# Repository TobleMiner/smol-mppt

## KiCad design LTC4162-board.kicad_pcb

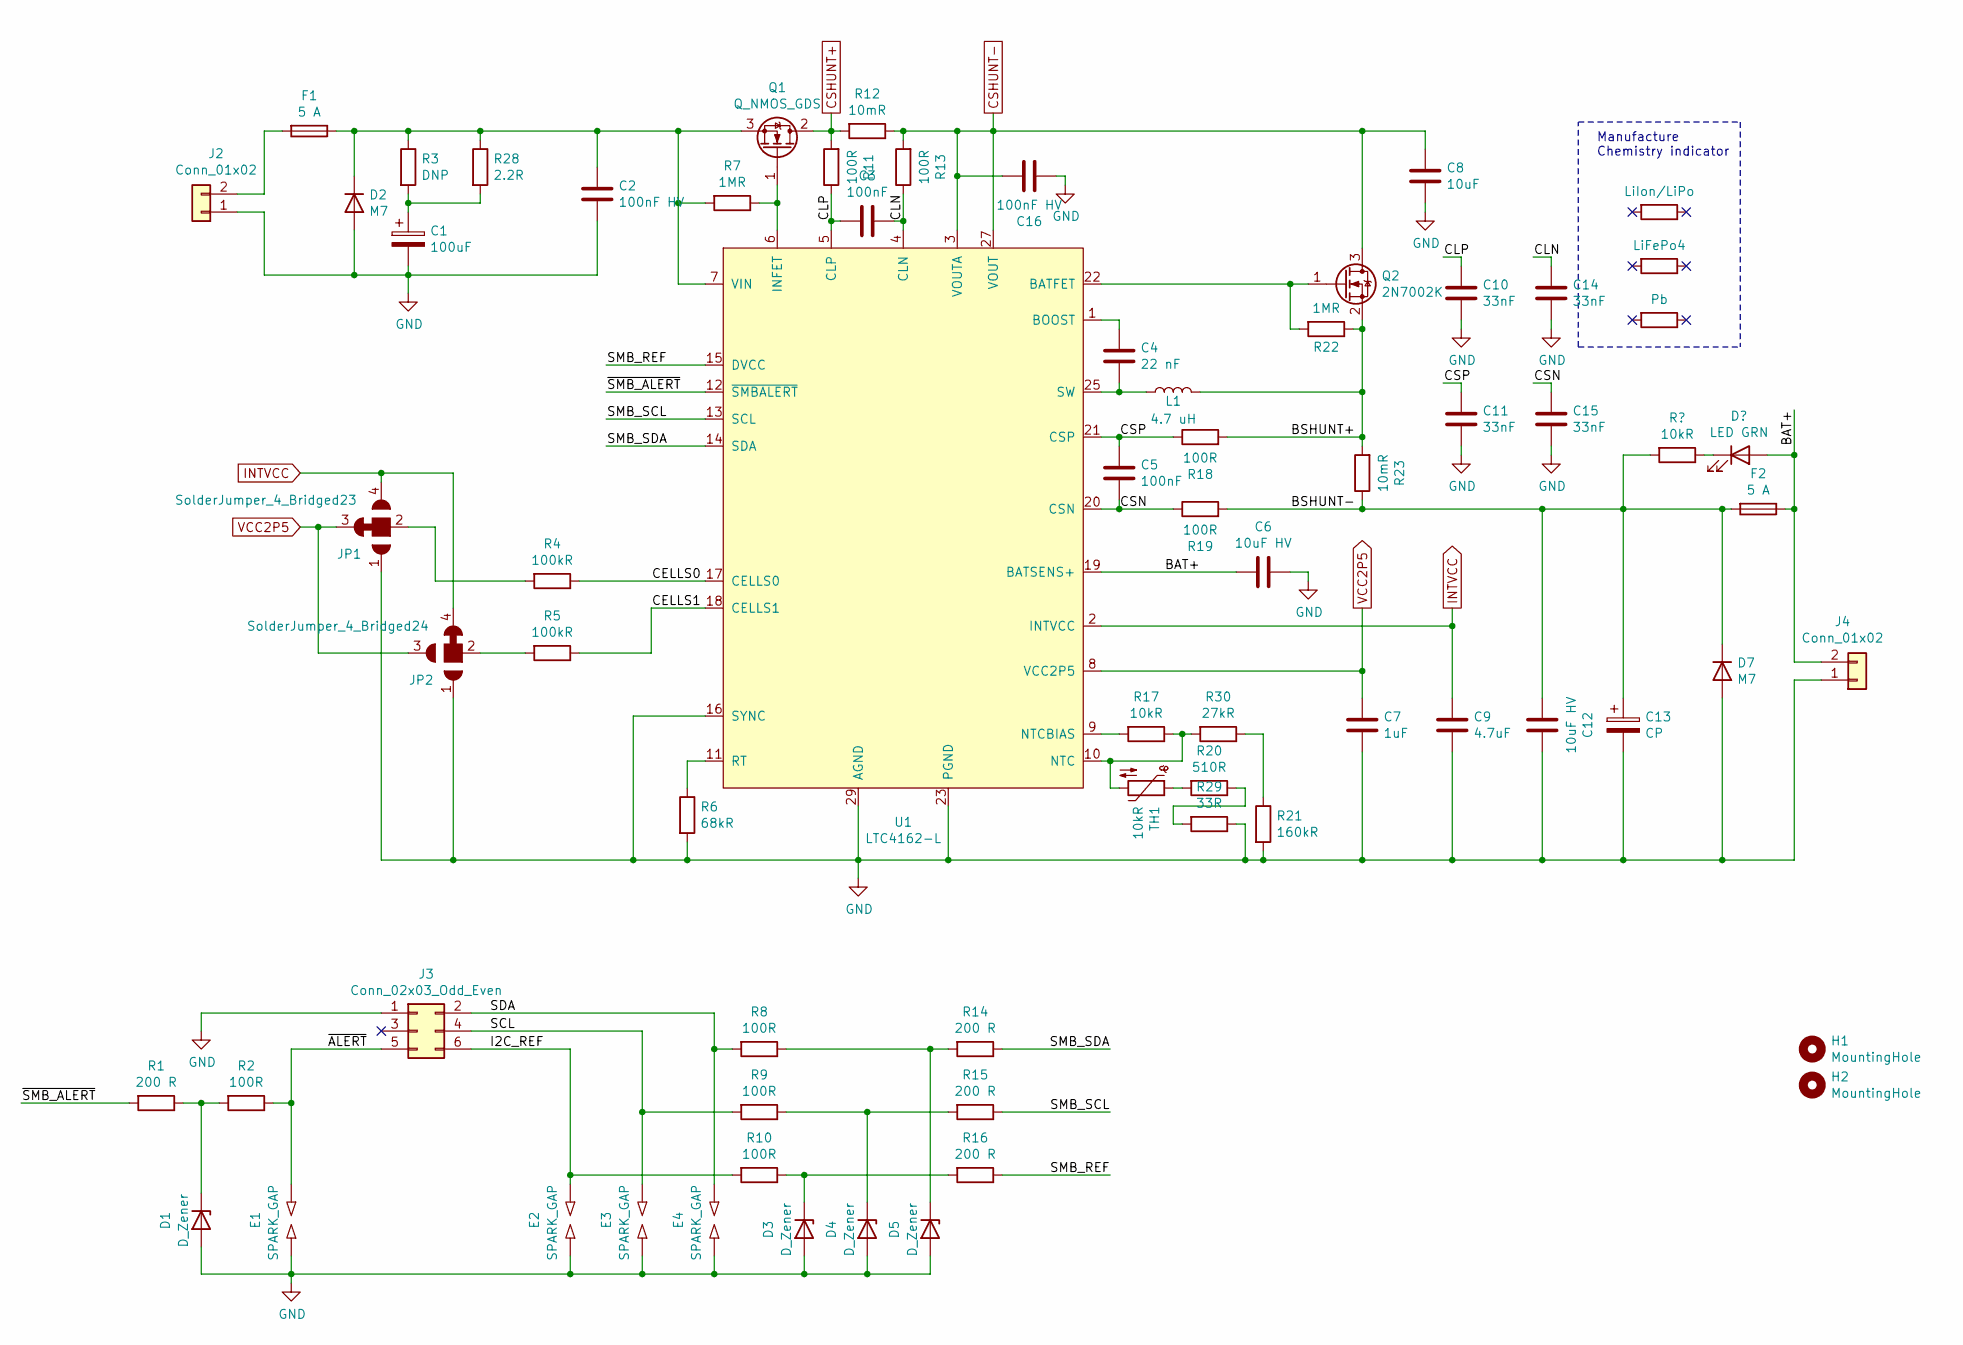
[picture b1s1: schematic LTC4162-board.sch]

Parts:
C1: 100uF; CP_Elec_10x10; LCSC C249996
C2, C16: 100nF HV; C_0603_1608Metric; LCSC C14663
C3, C5: 100nF; C_0402_1005Metric; LCSC C1525
C4: 22 nF; C_0402_1005Metric; LCSC C1532
C6, C12: 10uF HV; C_1206_3216Metric; LCSC C13585
C7: 1uF; C_0402_1005Metric; LCSC C52923
C8: 10uF; C_1206_3216Metric; LCSC C13585
C9: 4.7uF; C_0402_1005Metric; LCSC C23733
C10, C11, C14, C15: 33nF; C_0402_1005Metric; LCSC C1585
C13: CP; C_Elec_6.3x7.7; LCSC C249984
D1, D3, D4, D5: D_Zener; D_MiniMELF; LCSC C8062
D2, D7: M7; D_SMA; LCSC C95872
E1, E2, E3, E4: SPARK_GAP; spark-gap-0.2mm
F1, F2: 5 A; Fuse_1206_3216Metric; LCSC C182446
H1, H2: MountingHole; ToolingHole_JLCSMT
J2, J4: Conn_01x02; XT60
J3: Conn_02x03_Odd_Even; IDC-Header_2x03_P2.54mm_Vertical
JP1: SolderJumper_4_Bridged23; SolderJumper-4_P1.3mm_Bridged24_RoundedPad1.0x1.5mm
JP2: SolderJumper_4_Bridged24; SolderJumper-4_P1.3mm_Bridged23_RoundedPad1.0x1.5mm
L1: 4.7 uH; SLO0630H; LCSC C207840
Q1: Q_NMOS_GDS; TO-252-3_TabPin2; LCSC C194346
Q2: 2N7002K; SOT-23; LCSC C8545
R1, R14, R15, R16: 200 R; R_0402_1005Metric; LCSC C25087
R2, R8, R9, R10: 100R; R_0805_2012Metric; LCSC C17408
R3: DNP; R_1206_3216Metric
R4, R5: 100kR; R_0402_1005Metric; LCSC C25741
R6: 68kR; R_0402_1005Metric; LCSC C36871
R7, R22: 1MR; R_0402_1005Metric; LCSC C26083
R11, R13, R18, R19: 100R; R_0402_1005Metric; LCSC C25076
R12, R23: 10mR; R_1206_3216Metric; LCSC C26119
R17: 10kR; R_0402_1005Metric; LCSC C25744
R20: 510R; R_0402_1005Metric; LCSC C25123
R21: 160kR; R_0603_1608Metric; LCSC C22813
R24: LiIon/LiPo; R_0402_1005Metric
R25: LiFePo4; R_0402_1005Metric
R26: Pb; R_0402_1005Metric
R28: 2.2R; R_0805_2012Metric; LCSC C17521
R29: 33R; R_0402_1005Metric; LCSC C25105
R30: 27kR; R_0402_1005Metric; LCSC C25771
TH1: 10kR; R_0402_1005Metric; LCSC C92371
U1: LTC4162-L; QFN-28-1EP_4x5mm_P0.5mm_EP2.65x3.65mm_ThermalVias_backsolder

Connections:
/BAT+: C6.1, F2.1, J4.2, U1.19 (BATSENS+); also elsewhere on the board
/BSHUNT+: L1.2, Q2.2 (S), R18.2, R22.1, R23.2
/BSHUNT-: C12.1, C13.1, D7.1 (K), F2.2, R19.2, R23.1; also elsewhere on the board
/CELLS0: R4.1, U1.17 (CELLS0)
/CELLS1: R5.1, U1.18 (CELLS1)
/CLN: C3.2, C14.1, R13.1, U1.4 (CLN)
/CLP: C3.1, C10.1, R11.1, U1.5 (CLP)
/CSN: C5.2, C15.1, R19.1, U1.20 (CSN)
/CSP: C5.1, C11.1, R18.1, U1.21 (CSP)
/I2C_REF: E2.1, J3.6, R10.2
/SCL: E3.1, J3.4, R9.2
/SDA: E4.1, J3.2, R8.2
/SMB_REF: R16.1, U1.15 (DVCC)
/SMB_SCL: R15.1, U1.13 (SCL)
/SMB_SDA: R14.1, U1.14 (SDA)
/~ALERT: E1.1, J3.5, R2.1
/~SMB_ALERT: R1.2, U1.12 (~SMBALERT)
CSHUNT+: Q1.2 (D), R11.2, R12.2
CSHUNT-: C8.1, C16.2, Q2.3 (D), R12.1, R13.2, U1.3 (VOUTA), U1.27 (VOUT), U1.28 (VOUT)
GND: C1.2, C2.2, C6.2, C7.2, C8.2, C9.2, C10.2, C11.2, C12.2, C13.2, C14.2, C15.2, C16.1, D1.2 (A), D2.2 (A), D3.2 (A), D4.2 (A), D5.2 (A), D7.2 (A), E1.2, E2.2, E3.2, E4.2, J2.1, J3.1, J4.1, JP1.1, JP2.1, R6.2, R21.2, R29.1, U1.16 (SYNC), U1.23 (PGND), U1.24 (PGND), U1.29 (AGND)
INTVCC: C9.1, JP1.4, JP2.4, U1.2 (INTVCC)
unnamed: C1.1, R3.2, R28.2
unnamed: C2.1, D2.1 (K), F1.1, Q1.3 (S), R3.1, R7.2, R28.1, U1.7 (VIN)
unnamed: C4.1, U1.1 (BOOST)
unnamed: C4.2, L1.1, U1.25 (SW), U1.26 (SW)
unnamed: D1.1 (K), R1.1, R2.2
unnamed: D3.1 (K), R10.1, R16.2
unnamed: D4.1 (K), R9.1, R15.2
unnamed: D5.1 (K), R8.1, R14.2
unnamed: F1.2, J2.2
unnamed: JP1.2, R4.2
unnamed: JP2.2, R5.2
unnamed: Q1.1 (G), R7.1, U1.6 (INFET)
unnamed: Q2.1 (G), R22.2, U1.22 (BATFET)
unnamed: R6.1, U1.11 (RT)
unnamed: R17.1, R30.2, TH1.2, U1.10 (NTC)
unnamed: R17.2, U1.9 (NTCBIAS)
unnamed: R20.1, R29.2
unnamed: R20.2, TH1.1
unnamed: R21.1, R30.1
VCC2P5: C7.1, JP1.3, JP2.3, U1.8 (VCC2P5)

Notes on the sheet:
Manufacture Chemistry indicator

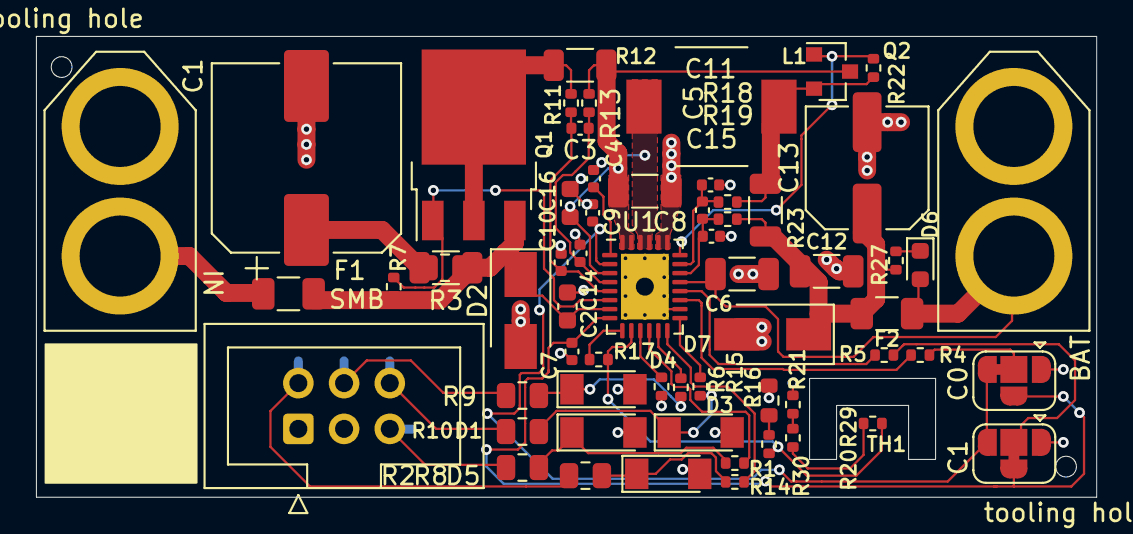
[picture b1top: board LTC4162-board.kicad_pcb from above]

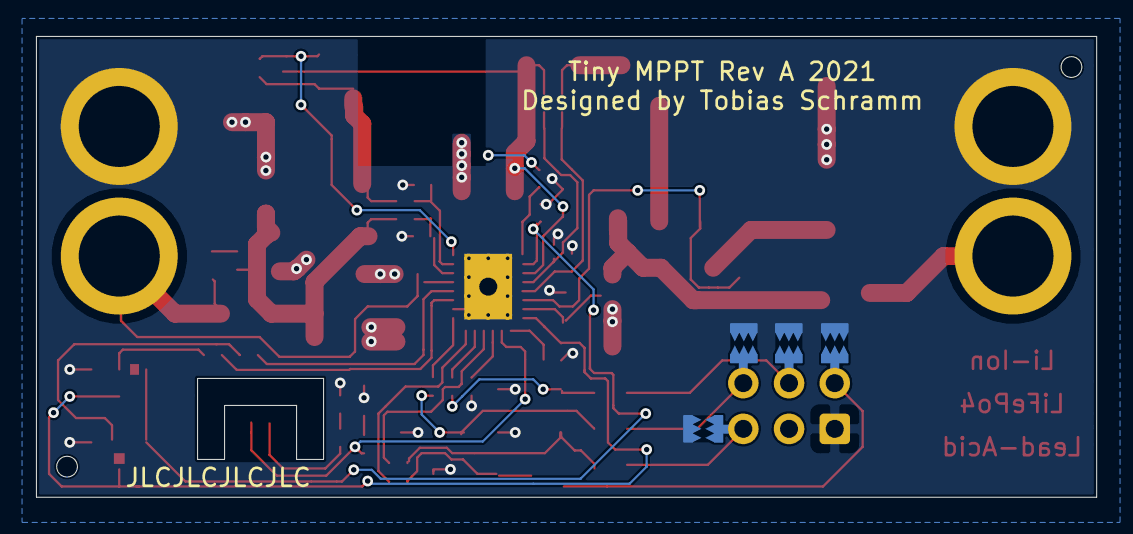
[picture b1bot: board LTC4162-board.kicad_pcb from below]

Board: 2 copper layers, 58.9 x 25.6 mm, 71 parts (4 on the bottom side), 42 nets.

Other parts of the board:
D6: LED GRN; LED_0603_1608Metric
R27: 10kR; R_0402_1005Metric

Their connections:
/BAT+: D6.2; also elsewhere on the board
/BSHUNT-: R27.2; also elsewhere on the board
unnamed: D6.1, R27.1

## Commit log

2021-02-17 Optimize for basic parts
2021-02-17 Export schematic as pdf
2021-02-17 Improve bypassing
    * Replace input wet electrolytic by solid polymer cap
    * Bypass charge output with wet electrolytic
    * Bypass both output and batsense+ with 10uF MLCC
